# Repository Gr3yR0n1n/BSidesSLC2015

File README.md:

# BSidesSLC 2015 Electronic Badge
[BSidesSLC](https://www.bsidesslc.org/), [theTransistor](http://thetransistor.com/), [DC801](https://www.dc801.org/), and [801 Labs](https://www.801labs.org/) brings you another fun conference badge.

**NOTE: The displays used in these badges are no longer being produced. They come from left over Nokia5110 units produced in China MANY years ago. Some of them have trouble working correctly. If you have this problem, we suggest gently pressing on the bottom of the LCDs metal frame. This sometimes helps reseat the internal display connector.**

##QuickSpecs
- Arduino bootloaded.
  - Any Atmega32u4 8mhz 3.3v bootloader will do.
  - We used the [Spark Fun Pro-Micro Bootloader and Arduino Hardware Files](https://www.sparkfun.com/products/12587)
- Atmel 32u4 mCU running at 8mhz on 3.3v
- Nokia 5110 LCD Display
  - 84px wide x 48px tall
  - Adjustable LED Backlight
  - Adjustable Contrast (via software)
- Controls
  - A (really) small 5 way Joypad
  - 2 Action Buttons
- Extra IO
  - Extra GPIO has been conveniently been broken-out on the bottom-edge of the board.
- Power
  - Selectable USB / 2x AAA Battery Power

##Reprogramming
Reprogramming can be done either over USB via the Arduino IDE, or over the serial "HACK" ISP breakout. To use the Arduino programming over USB, you will need to copy 8mhz Atmega32u4 hardware files into the "hardware" folder in your Arduino installation. See the SparkFun link above for more information.

##Credits:

**Electronics Work & Processing**
- Compukidmike
- Devino

**QA, Assembly, & Loading**
- l3mur (aka aarobc)
- Nemus
- Compukidmike
- Yukaia

**Original Design, Code, & Mgmt**
- D3c4f

**Special Thanks**
- Nemus
- T4rkus & BSidesSLC

##Questions and Comments
Questions and comments can be directed twards the following forms of communication:
- \#dc801 on freenode
- d3c4f [at] thetransistor [dot] com

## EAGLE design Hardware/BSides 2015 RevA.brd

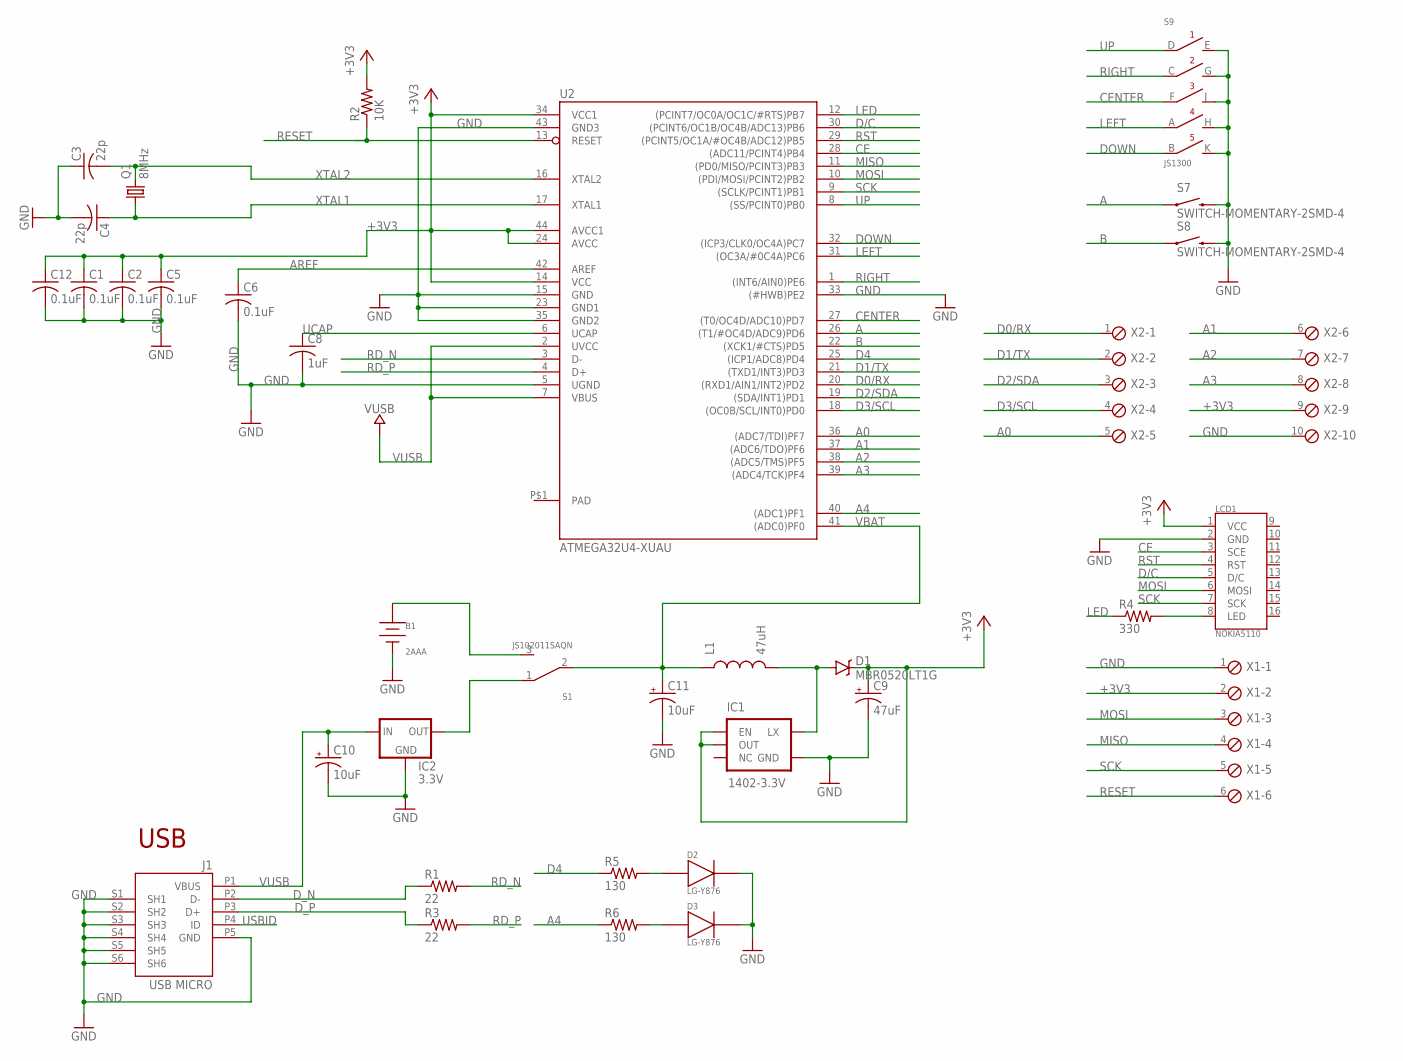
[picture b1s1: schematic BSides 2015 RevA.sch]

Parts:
B1: 2AAA
C1, C2, C5, C6, C12: 0.1uF; C0603K
C3, C4: 22p; C0603K
C8: 1uF; C0603K
C9: 47uF; 6032
C10, C11: 10uF; EIA3216
D1: MBR0520LT1G; SOD-123
D2, D3: LG-Y876
IC1: 1402-3.3V; SOT23-5
IC2: 3.3V; SOT23
J1: USB MICRO; CON2_USB_MICRO_B_AT
L1: 47uH; NR6028
LCD1: NOKIA5110; 5110
Q1: 8MHz; SM49
R1, R3: 22; R0603
R2: 10K; R0603
R4: 330; R0603
R5, R6: 130; R0603
S1: JS102011SAQN; SAQN
S7, S8: SWITCH-MOMENTARY-2SMD-4; TACTILE_SWITCH_TALL
S9: JS1300
U2: ATMEGA32U4-XUAU; TQFP44-PAD
X1: MPT6; 6POL254
X2: MPT10; 10POL254

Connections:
+3V3: C1.1, C2.1, C5.1, C9.P$2 (+), C12.1, D1.P$1 (C), IC1.1 (EN), IC1.2 (OUT), LCD1.1 (VCC), R2.2, U2.14 (VCC), U2.24 (AVCC), U2.34 (VCC1), U2.44 (AVCC1), X1.2, X2.9
A: S7.A2 (1), U2.26 ((T1/#OC4D/ADC9)PD6)
A0: U2.36 ((ADC7/TDI)PF7), X2.5
A1: U2.37 ((ADC6/TDO)PF6), X2.6
A2: U2.38 ((ADC5/TMS)PF5), X2.7
A3: U2.39 ((ADC4/TCK)PF4), X2.8
A4: R6.1, U2.40 ((ADC1)PF1)
AREF: C6.1, U2.42 (AREF)
B: S8.A2 (1), U2.22 ((XCK1/#CTS)PD5)
CE: LCD1.3 (SCE), U2.28 ((ADC11/PCINT4)PB4)
CENTER: S9.F, U2.27 ((T0/OC4D/ADC10)PD7)
D0/RX: U2.20 ((RXD1/AIN1/INT2)PD2), X2.1
D1/TX: U2.21 ((TXD1/INT3)PD3), X2.2
D2/SDA: U2.19 ((SDA/INT1)PD1), X2.3
D3/SCL: U2.18 ((OC0B/SCL/INT0)PD0), X2.4
D4: R5.1, U2.25 ((ICP1/ADC8)PD4)
D/C: LCD1.5 (D/C), U2.30 ((PCINT6/OC1B/OC4B/ADC13)PB6)
DOWN: S9.B, U2.32 ((ICP3/CLK0/OC4A)PC7)
D_N: J1.P2 (D-), R1.1
D_P: J1.P3 (D+), R3.1
GND: B1.-, C1.2, C2.2, C3.1, C4.2, C5.2, C6.2, C8.2, C9.P$1 (-), C10.C (-), C11.C (-), C12.2, D2.C, D3.C, IC1.4 (GND), IC2.1 (GND), J1.P5 (GND), J1.S1 (SH1), J1.S2 (SH2), J1.S3 (SH3), J1.S4 (SH4), J1.S5 (SH5), J1.S6 (SH6), LCD1.2 (GND), S7.B2 (2), S8.B2 (2), S9.E, S9.G, S9.H, S9.J, S9.K, U2.5 (UGND), U2.15 (GND), U2.23 (GND1), U2.33 ((#HWB)PE2), U2.35 (GND2), U2.43 (GND3), X1.1, X2.10
LED: R4.1, U2.12 ((PCINT7/OC0A/OC1C/#RTS)PB7)
LEFT: S9.A, U2.31 ((OC3A/#0C4A)PC6)
MISO: U2.11 ((PD0/MISO/PCINT3)PB3), X1.4
MOSI: LCD1.6 (MOSI), U2.10 ((PDI/MOSI/PCINT2)PB2), X1.3
unnamed: D1.P$2 (A), IC1.5 (LX), L1.P$2 (2)
unnamed: IC2.2 (OUT), S1.1
unnamed: B1.+, S1.3
unnamed: LCD1.8 (LED), R4.2
unnamed: D2.A, R5.2
unnamed: D3.A, R6.2
PAD: U2.P$1 (PAD)
RD_N: R1.2, U2.3 (D-)
RD_P: R3.2, U2.4 (D+)
RESET: R2.1, U2.13 (RESET), X1.6
RIGHT: S9.C, U2.1 ((INT6/AIN0)PE6)
RST: LCD1.4 (RST), U2.29 ((PCINT5/OC1A/#OC4B/ADC12)PB5)
SCK: LCD1.7 (SCK), U2.9 ((SCLK/PCINT1)PB1), X1.5
UCAP: C8.1, U2.6 (UCAP)
UP: S9.D, U2.8 ((SS/PCINT0)PB0)
USBID: J1.P4 (ID)
VBAT: C11.A (+), L1.P$1 (1), S1.2, U2.41 ((ADC0)PF0)
VUSB: C10.A (+), IC2.3 (IN), J1.P1 (VBUS), U2.2 (UVCC), U2.7 (VBUS)
XTAL1: C4.1, Q1.1, U2.17 (XTAL1)
XTAL2: C3.2, Q1.2, U2.16 (XTAL2)

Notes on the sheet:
USB

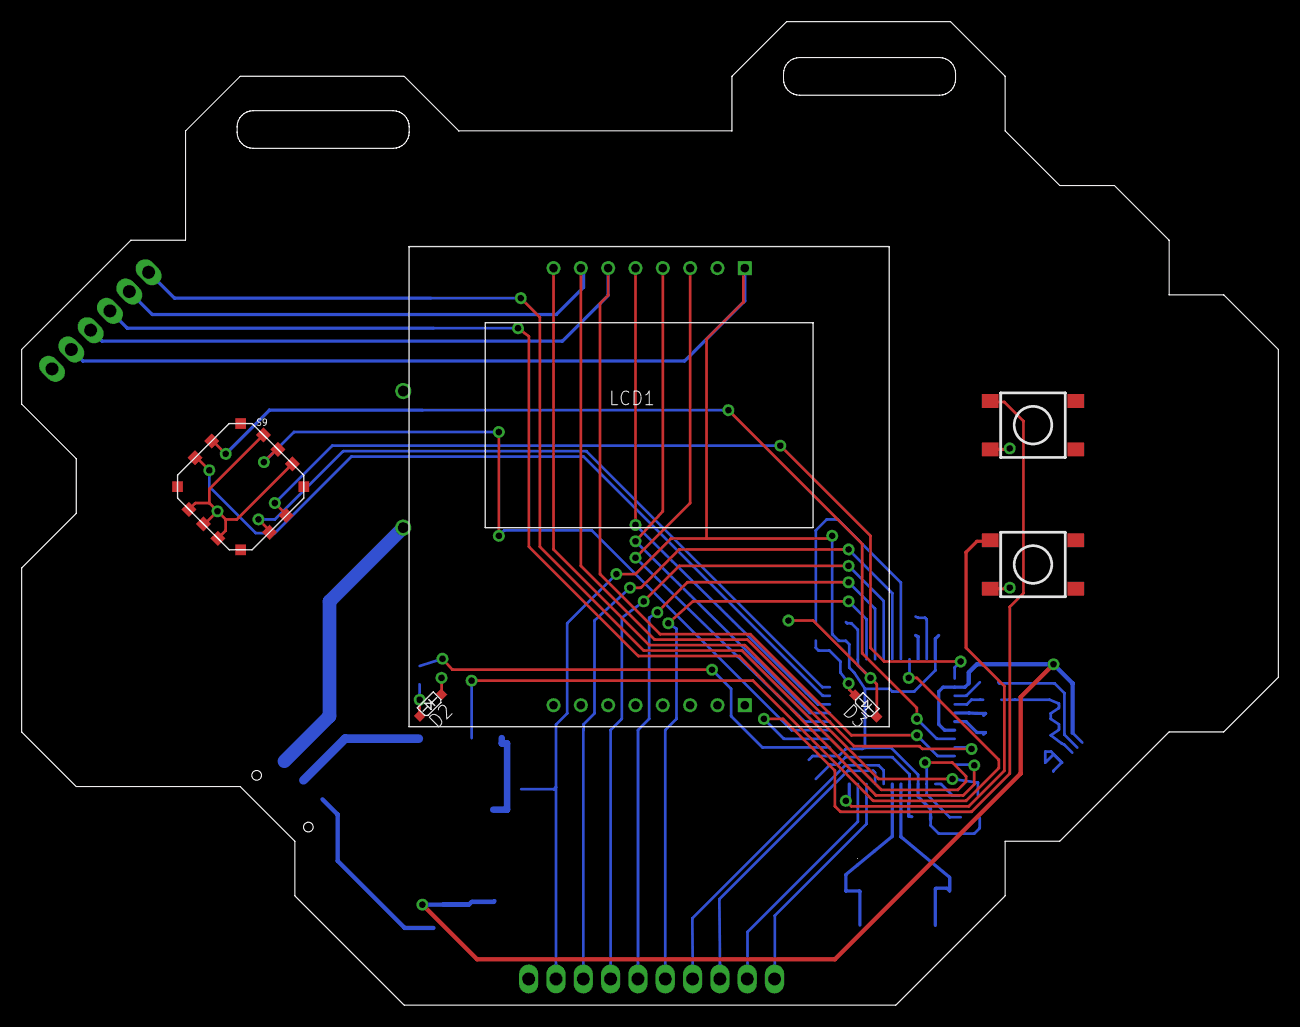
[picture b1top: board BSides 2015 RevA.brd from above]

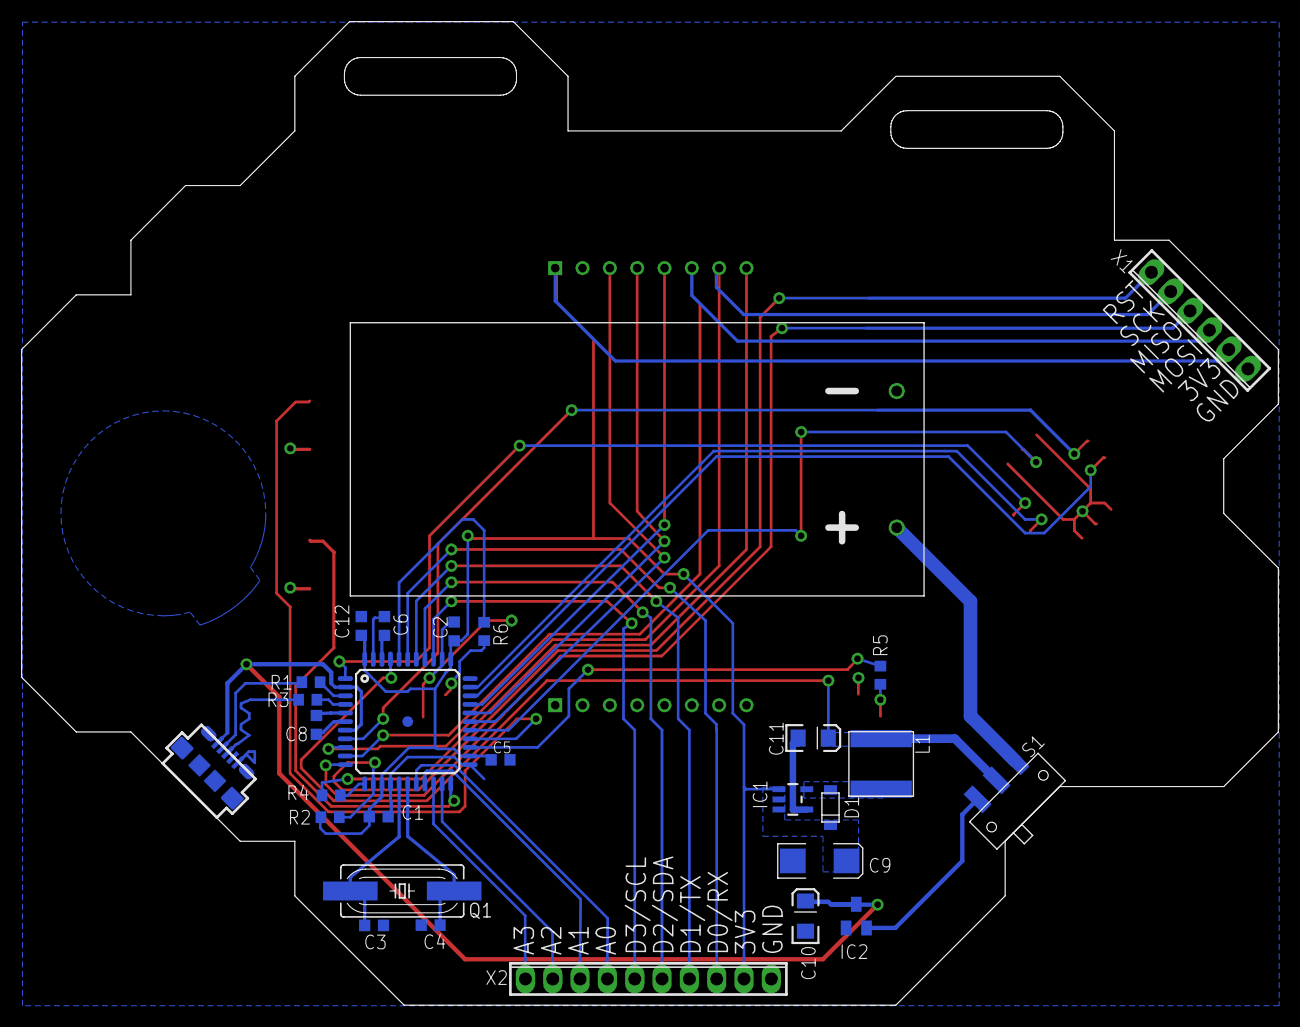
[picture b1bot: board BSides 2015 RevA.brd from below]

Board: 4 copper layers, 116.8 x 91.4 mm, 34 parts (28 on the bottom side), 43 nets.

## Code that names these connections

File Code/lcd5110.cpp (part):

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#include "bitmaps.h"

/*
SCE      : PB4
RESET    : PB5
DC       : PB6
SDIN     : PB2
SCLK     : PB1
LED Back : Arduino Analog 11 (PWM)
*/

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
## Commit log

2015-03-20 Initial commit
    Now with actual files! :)
2015-03-20 Updated the Readme
2015-03-20 More small Readme changes
2015-03-20 More small readme updates
2015-03-20 Move Arduino files for make Arduino IDE easier to work with.
2015-03-20 Added links to the readme

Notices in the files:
parts and their libraries:
SparkFun-PowerIC: Licensing: Creative Commons ShareAlike 4.0 International - https://creativecommons.org/licenses/by-sa/4.0
